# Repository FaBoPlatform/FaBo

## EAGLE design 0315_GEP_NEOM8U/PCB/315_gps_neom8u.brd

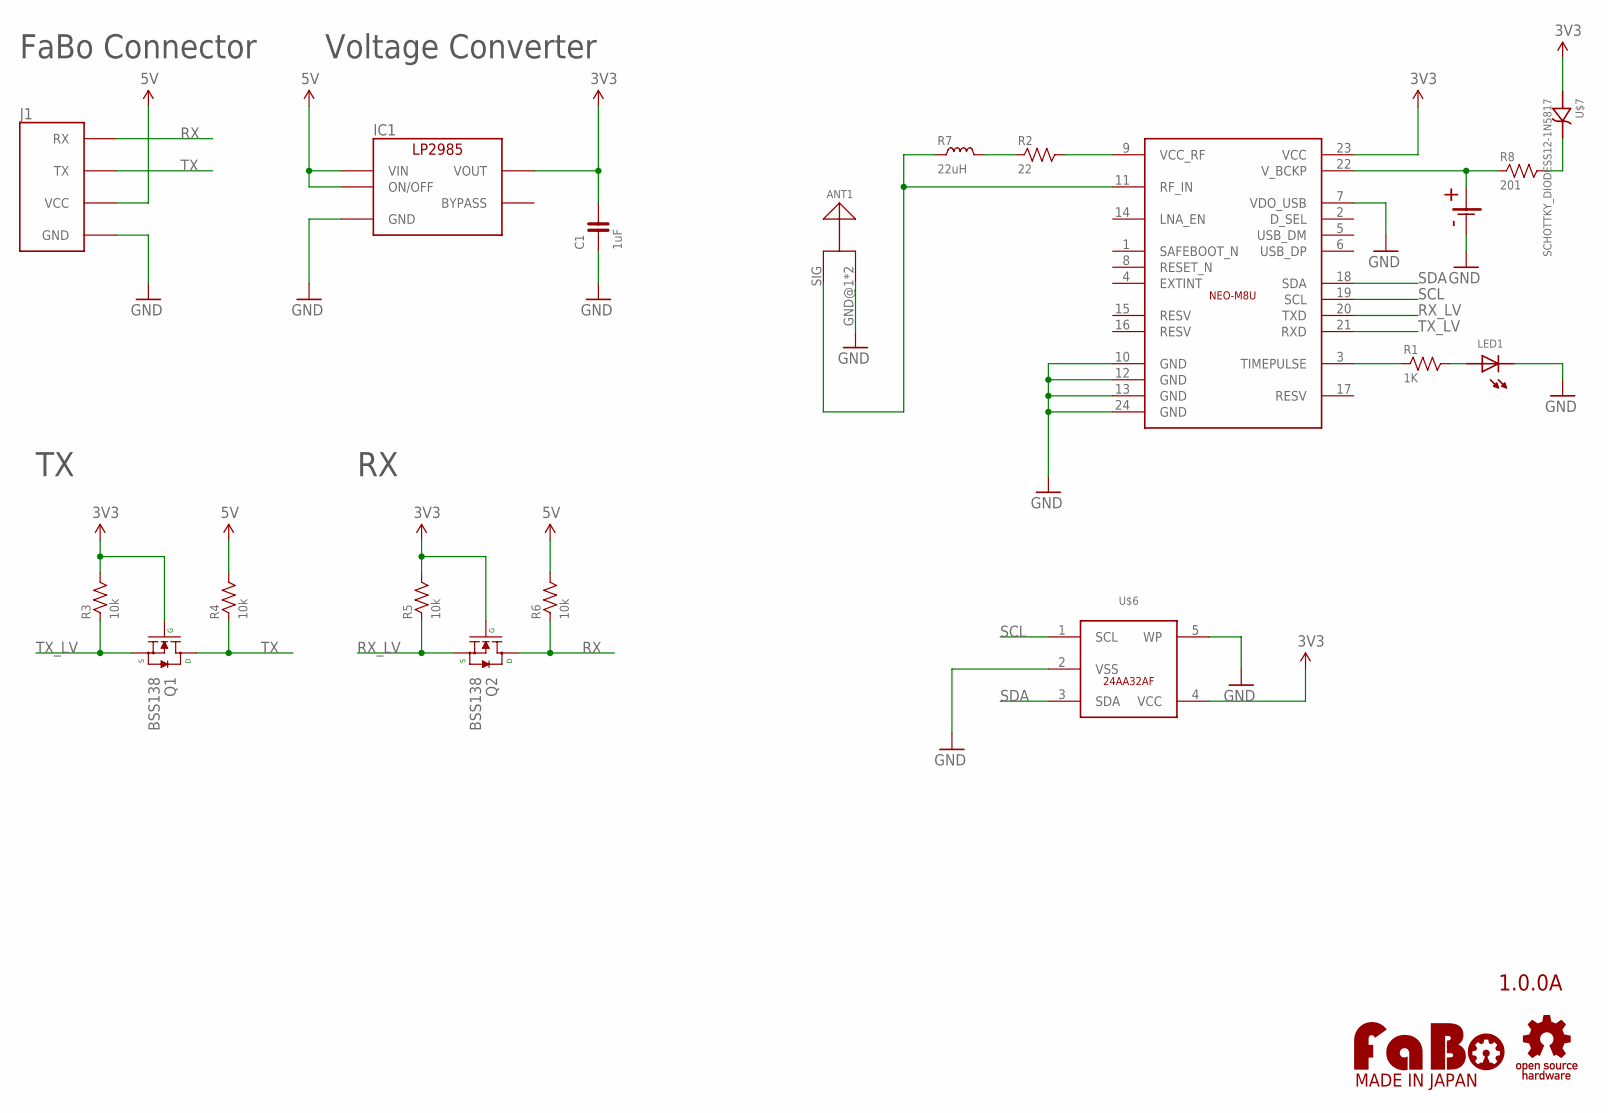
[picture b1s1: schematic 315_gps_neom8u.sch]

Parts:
ANT1: ANTENA_HIROSE-UF-L; HIROSE-UF-L
C1: 1uF; 0603-NARROW
IC1: LP2985-33DBV; SOT-23-5
J1: FABO_BRICK_SERIAL
LED1: LED-0603; 0603
Q1, Q2: BSS138; SOT23-3
R1: 1K; 0603-NARROW
R2: 22; 0603-NARROW
R3, R4, R5, R6: 10k; 0603-NARROW
R7: 22uH; 0603
R8: 201; 0603-NARROW
U$2: LOGO_OSHW-M_BOTTOM; LOGO_OSHW_M_BOTTOM
U$3: LOGO_FABO-M_BOTTOM; LOGO_FABO_MS_BOTTOM
U$4: NEO-M8U; NEO-M8M
U$6: 24AA32AF
U$7: SCHOTTKY_DIODESS12-1N5817; DO-214AC
U$10: COILCELLBK-885-BOTTOM; BK-885

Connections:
3V3: C1.2, IC1.5 (VOUT), Q1.1 (G), Q2.1 (G), R3.2, R5.2, U$4.23 (VCC), U$6.4 (VCC), U$7.CATHODE
5V: IC1.1 (VIN), IC1.3 (ON/OFF), J1.VCC, R4.2, R6.2
GND: ANT1.GND@1 (GND), ANT1.GND@2 (GND), C1.1, IC1.2 (GND), J1.GND, LED1.CATHODE, U$4.7 (VDO_USB), U$4.10 (GND), U$4.12 (GND), U$4.13 (GND), U$4.24 (GND), U$6.2 (VSS), U$6.5 (WP), U$10.GND1 (-), U$10.GND2 (-)
unnamed: R1.1, U$4.3 (TIMEPULSE)
unnamed: LED1.ANODE, R1.2
unnamed: R8.2, U$7.ANODE
unnamed: R8.1, U$4.22 (V_BCKP), U$10.VCC (+)
unnamed: R2.2, U$4.9 (VCC_RF)
unnamed: R2.1, R7.2
unnamed: ANT1.SIG, R7.1, U$4.11 (RF_IN)
RX: J1.RX, Q2.3 (D), R6.1
RX_LV: Q2.2 (S), R5.1, U$4.20 (TXD)
SCL: U$4.19 (SCL), U$6.1 (SCL)
SDA: U$4.18 (SDA), U$6.3 (SDA)
TX: J1.TX, Q1.3 (D), R4.1
TX_LV: Q1.2 (S), R3.1, U$4.21 (RXD)

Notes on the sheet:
1.0.0A
Voltage Converter
FaBo Connector

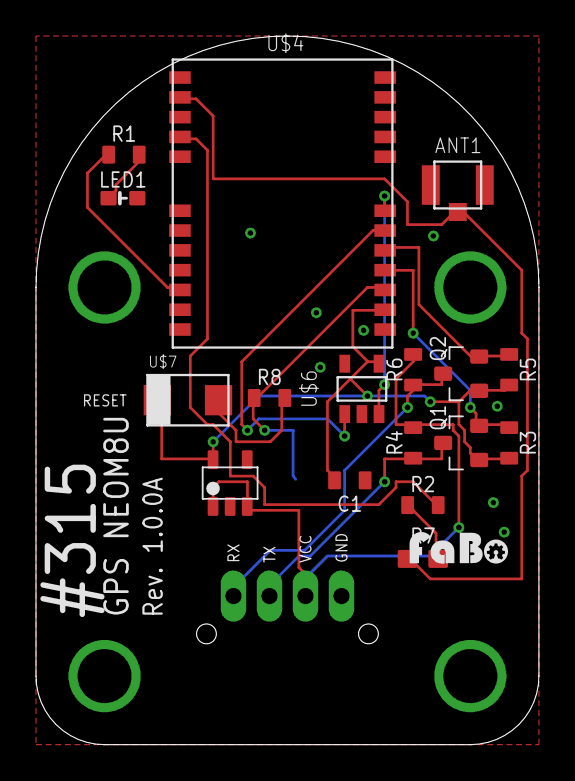
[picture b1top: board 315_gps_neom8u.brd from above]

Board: 2 copper layers, 27.9 x 39.4 mm, 22 parts (0 on the bottom side), 16 nets.

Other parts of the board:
U$5: LOGO_FABO_S

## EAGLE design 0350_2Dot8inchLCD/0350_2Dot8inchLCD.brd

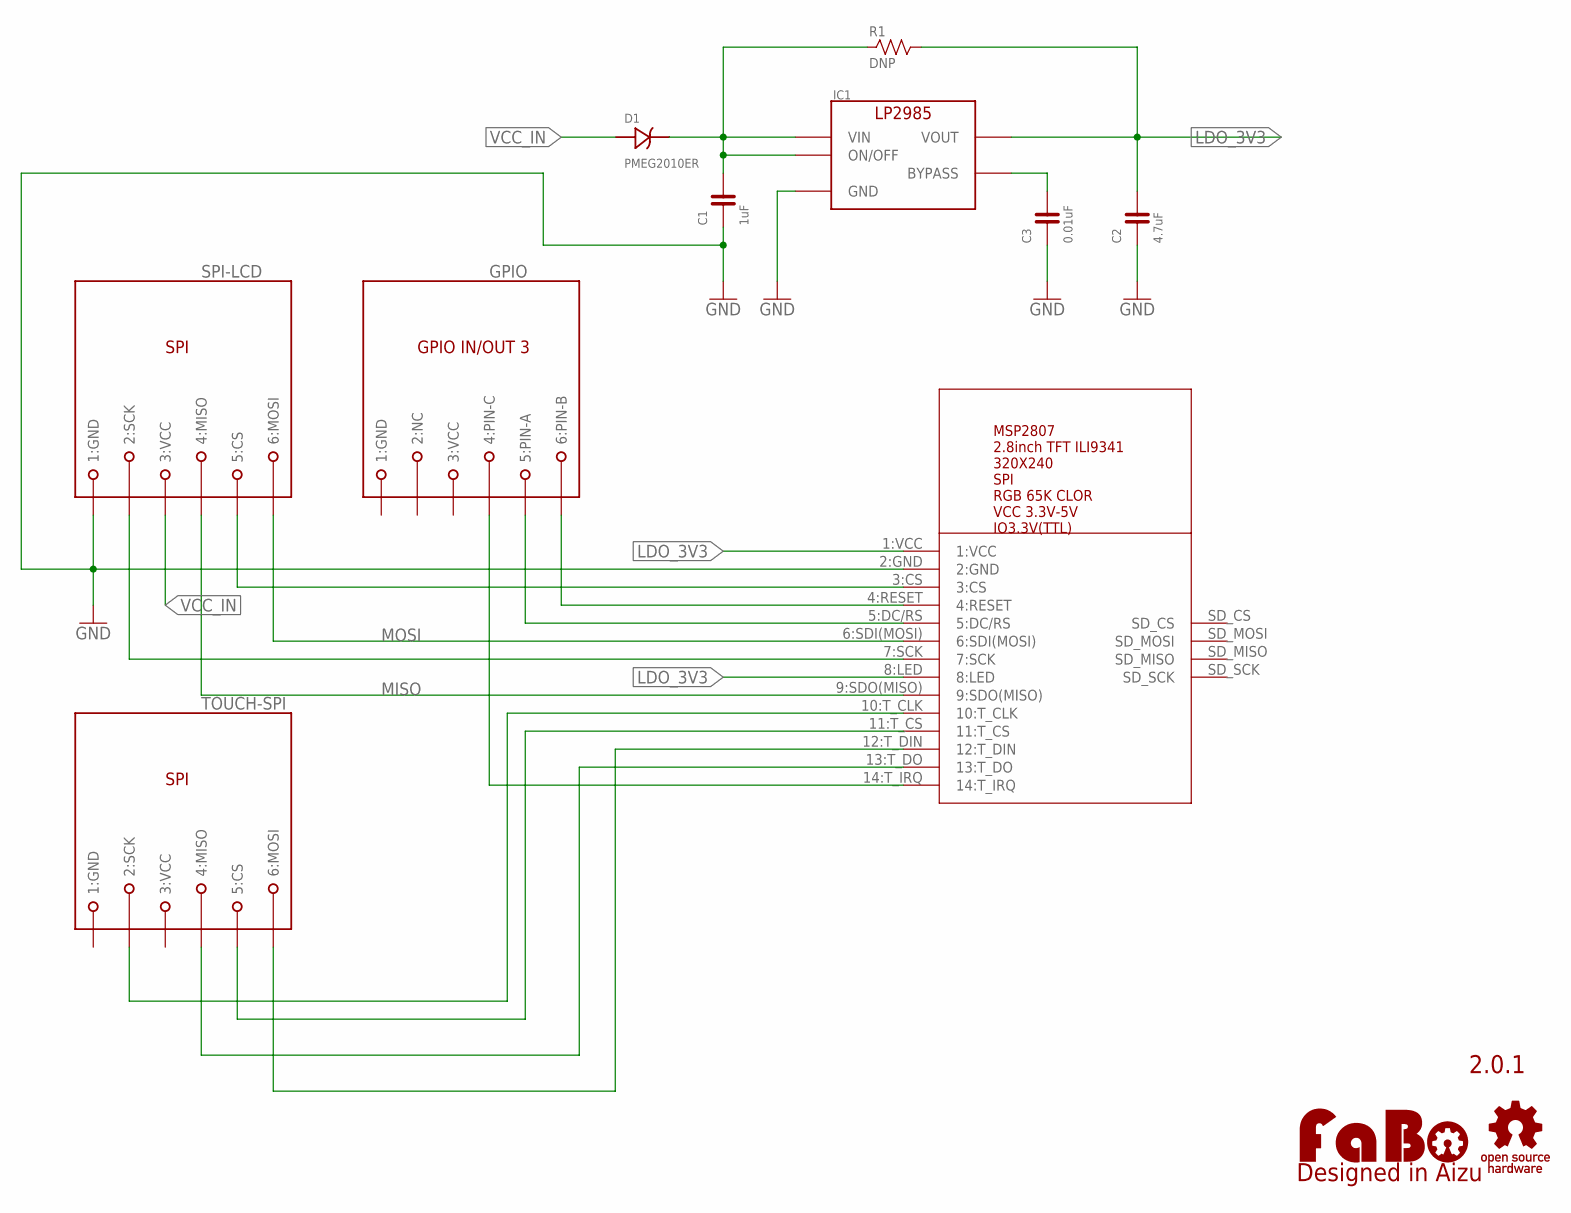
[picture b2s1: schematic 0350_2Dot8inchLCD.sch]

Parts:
C1: 1uF; 0603
C2: 4.7uF; 0603
C3: 0.01uF; 0603
D1: PMEG2010ER; SOD123W
GPIO: MODULAR-JACK-6P-RJ11_GPIO3; 7002-6PXC-X
IC1: LP2985-33DBV; SOT-23-5
LOGO1: LOGO_FABO-M_BOTTOM; LOGO_FABO_M_BOTTOM
R1: DNP; 0805
SPI-LCD: MODULAR-JACK-6P-RJ11_SPI; 7002-6PXC-X
TOUCH-SPI: MODULAR-JACK-6P-RJ11_SPI; 7002-6PXC-X
U$3: LOGO_OSHW-M_BOTTOM; LOGO_OSHW_M_BOTTOM
U$5: MSP2807(LCD_SPI); SPI_LCD_MSP2807

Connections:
1:GND: GPIO.1 (1:GND), TOUCH-SPI.1 (1:GND)
3:VCC: GPIO.3 (3:VCC), TOUCH-SPI.3 (3:VCC)
GND: C1.1, C2.1, C3.1, IC1.2 (GND), SPI-LCD.1 (1:GND), U$5.2:GND
LDO_3V3: C2.2, IC1.5 (VOUT), R1.2, U$5.1:VCC, U$5.8:LED
MISO: SPI-LCD.4 (4:MISO), U$5.9:SDO(MISO)
MOSI: SPI-LCD.6 (6:MOSI), U$5.6:SDI(MOSI)
unnamed: C1.2, D1.1 (CATHODE), IC1.1 (VIN), IC1.3 (ON/OFF), R1.1
unnamed: C3.2, IC1.4 (BYPASS)
unnamed: SPI-LCD.2 (2:SCK), U$5.7:SCK
unnamed: SPI-LCD.5 (5:CS), U$5.3:CS
unnamed: GPIO.6 (6:PIN-B), U$5.4:RESET
unnamed: GPIO.5 (5:PIN-A), U$5.5:DC/RS
unnamed: TOUCH-SPI.2 (2:SCK), U$5.10:T_CLK
unnamed: TOUCH-SPI.5 (5:CS), U$5.11:T_CS
unnamed: TOUCH-SPI.4 (4:MISO), U$5.13:T_DO
unnamed: TOUCH-SPI.6 (6:MOSI), U$5.12:T_DIN
unnamed: GPIO.4 (4:PIN-C), U$5.14:T_IRQ
VCC_IN: D1.2 (ANODE), SPI-LCD.3 (3:VCC)

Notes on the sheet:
2.0.1

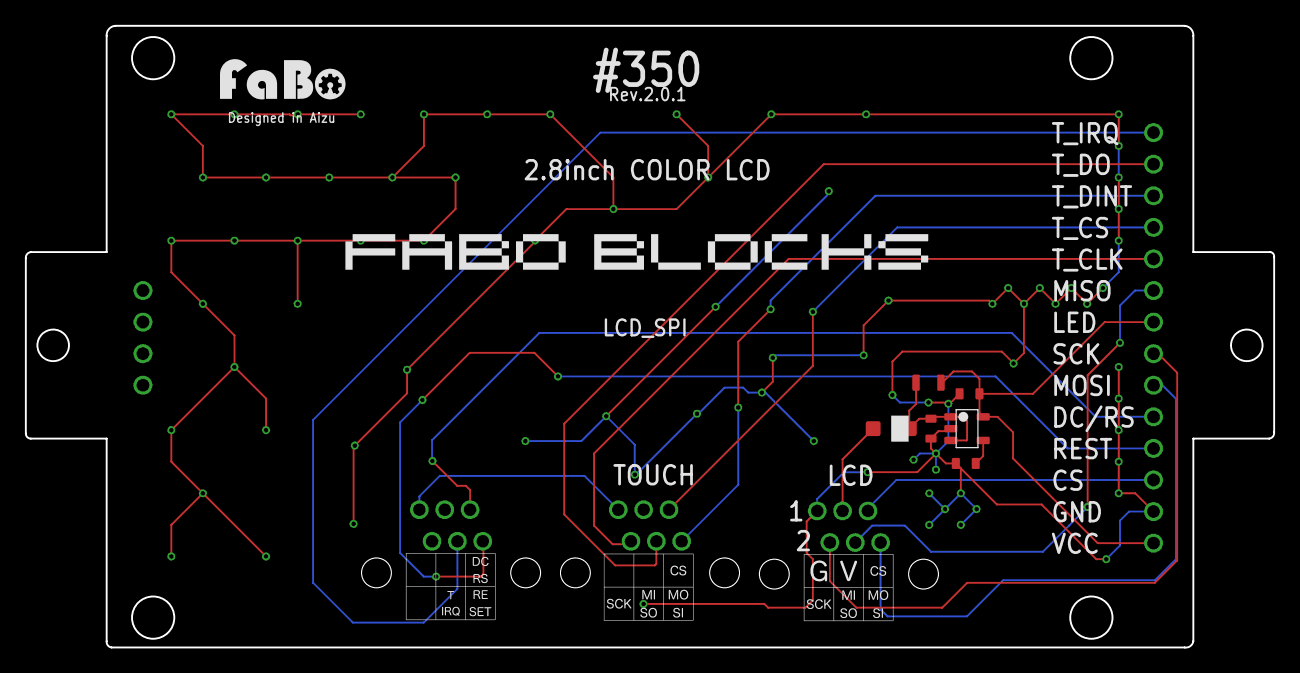
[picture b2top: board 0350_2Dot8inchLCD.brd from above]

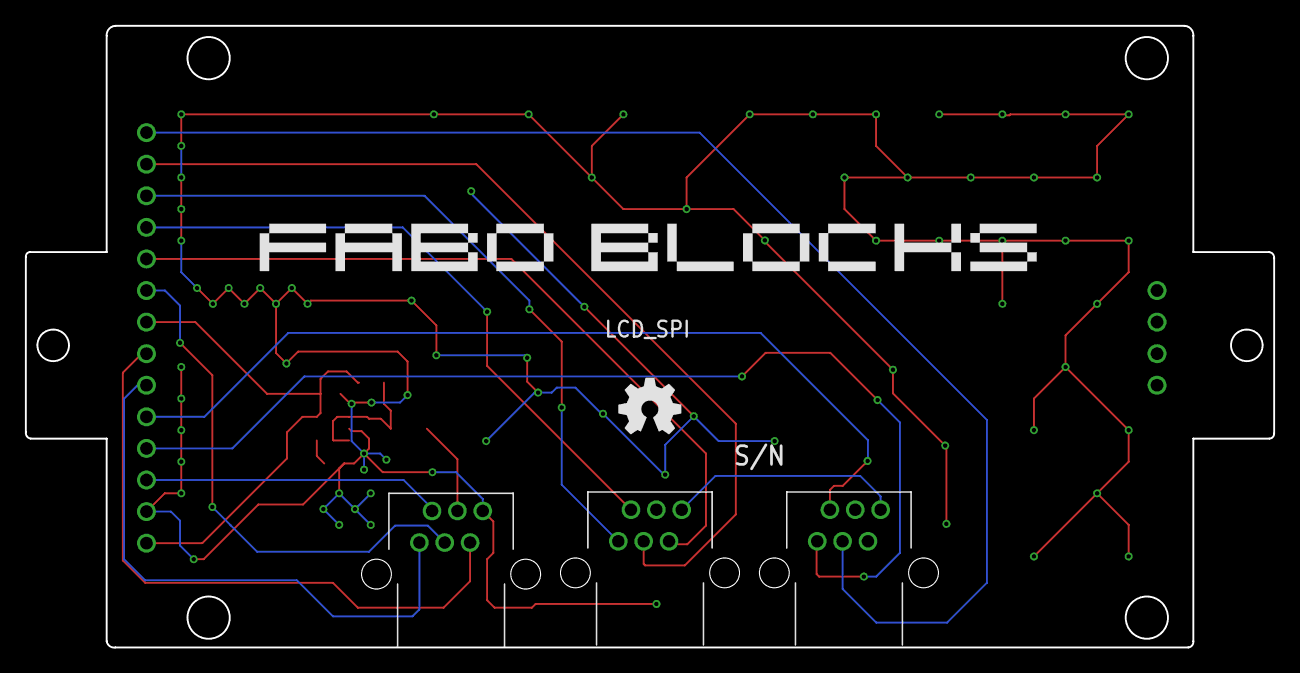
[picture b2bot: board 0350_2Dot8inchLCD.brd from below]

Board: 2 copper layers, 100.4 x 50.0 mm, 14 parts (4 on the bottom side), 18 nets.

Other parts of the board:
U$2, U$4: 4-1BLOCK

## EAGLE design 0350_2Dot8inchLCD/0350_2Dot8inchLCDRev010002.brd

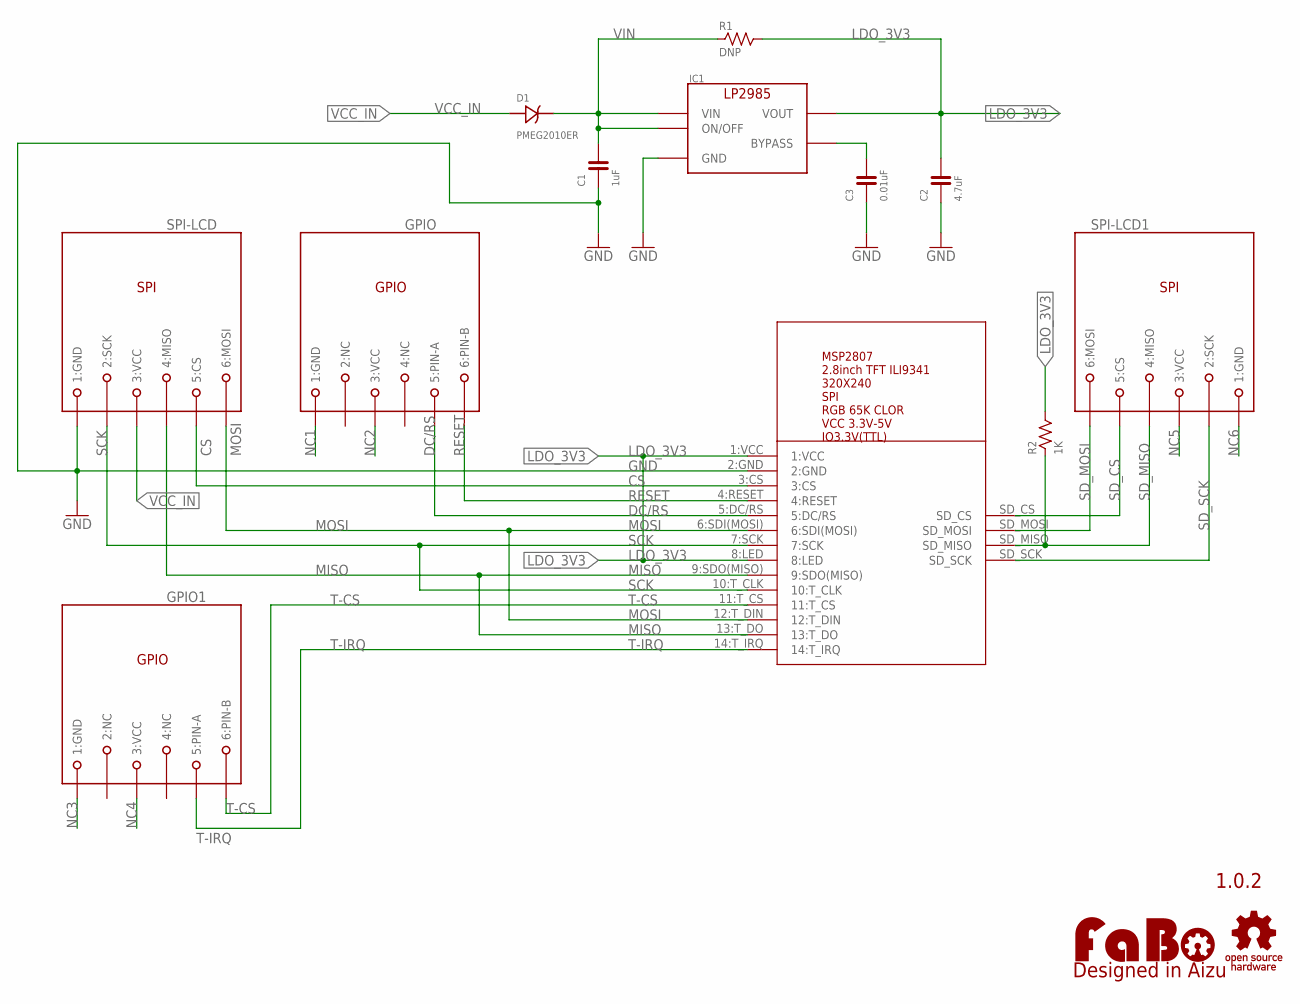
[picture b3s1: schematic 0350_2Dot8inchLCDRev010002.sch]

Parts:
C1: 1uF; 0603
C2: 4.7uF; 0603
C3: 0.01uF; 0603
D1: PMEG2010ER; SOD123W
GPIO, GPIO1: MODULAR-JACK-6P-RJ11_GPIO; 7002-6PXC-X
IC1: LP2985-33DBV; SOT-23-5
LOGO1: LOGO_FABO-M_BOTTOM; LOGO_FABO_M_BOTTOM
R1: DNP; 0805
R2: 1K; 0805
SPI-LCD, SPI-LCD1: MODULAR-JACK-6P-RJ11_SPI; 7002-6PXC-X
U$3: LOGO_OSHW-M_BOTTOM; LOGO_OSHW_M_BOTTOM
U$6: MSP2807(LCD_SPI_WITH_SDCARD; SPI_LCD_MSP2807

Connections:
CS: SPI-LCD.5 (5:CS), U$6.3:CS
DC/RS: GPIO.5 (5:PIN-A), U$6.5:DC/RS
GND: C1.1, C2.1, C3.1, IC1.2 (GND), SPI-LCD.1 (1:GND), U$6.2:GND
LDO_3V3: C2.2, IC1.5 (VOUT), R1.2, R2.2, U$6.1:VCC, U$6.8:LED
MISO: SPI-LCD.4 (4:MISO), U$6.9:SDO(MISO), U$6.13:T_DO
MOSI: SPI-LCD.6 (6:MOSI), U$6.6:SDI(MOSI), U$6.12:T_DIN
unnamed: C3.2, IC1.4 (BYPASS)
NC1: GPIO.1 (1:GND)
NC2: GPIO.3 (3:VCC)
NC3: GPIO1.1 (1:GND)
NC4: GPIO1.3 (3:VCC)
NC5: SPI-LCD1.3 (3:VCC)
NC6: SPI-LCD1.1 (1:GND)
RESET: GPIO.6 (6:PIN-B), U$6.4:RESET
SCK: SPI-LCD.2 (2:SCK), U$6.7:SCK, U$6.10:T_CLK
SD_CS: SPI-LCD1.5 (5:CS), U$6.SD_CS
SD_MISO: R2.1, SPI-LCD1.4 (4:MISO), U$6.SD_MISO
SD_MOSI: SPI-LCD1.6 (6:MOSI), U$6.SD_MOSI
SD_SCK: SPI-LCD1.2 (2:SCK), U$6.SD_SCK
T-CS: GPIO1.6 (6:PIN-B), U$6.11:T_CS
T-IRQ: GPIO1.5 (5:PIN-A), U$6.14:T_IRQ
VCC_IN: D1.2 (ANODE), SPI-LCD.3 (3:VCC)
VIN: C1.2, D1.1 (CATHODE), IC1.1 (VIN), IC1.3 (ON/OFF), R1.1

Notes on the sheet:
1.0.2

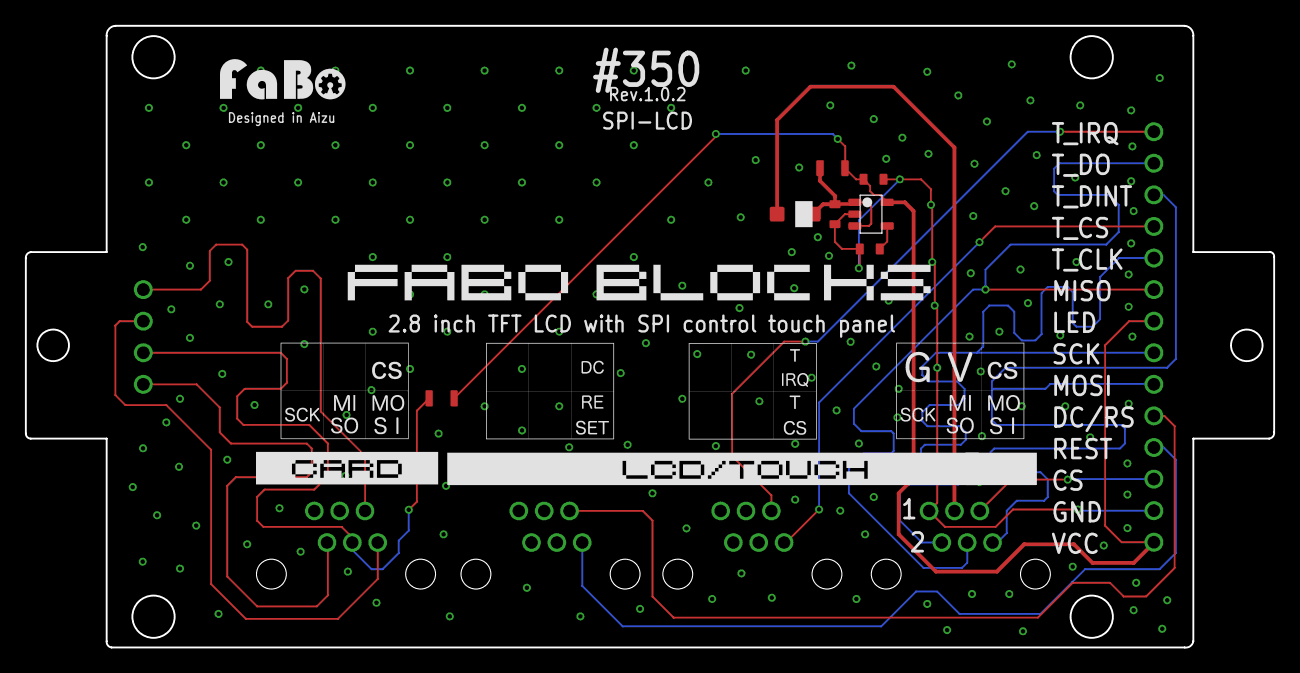
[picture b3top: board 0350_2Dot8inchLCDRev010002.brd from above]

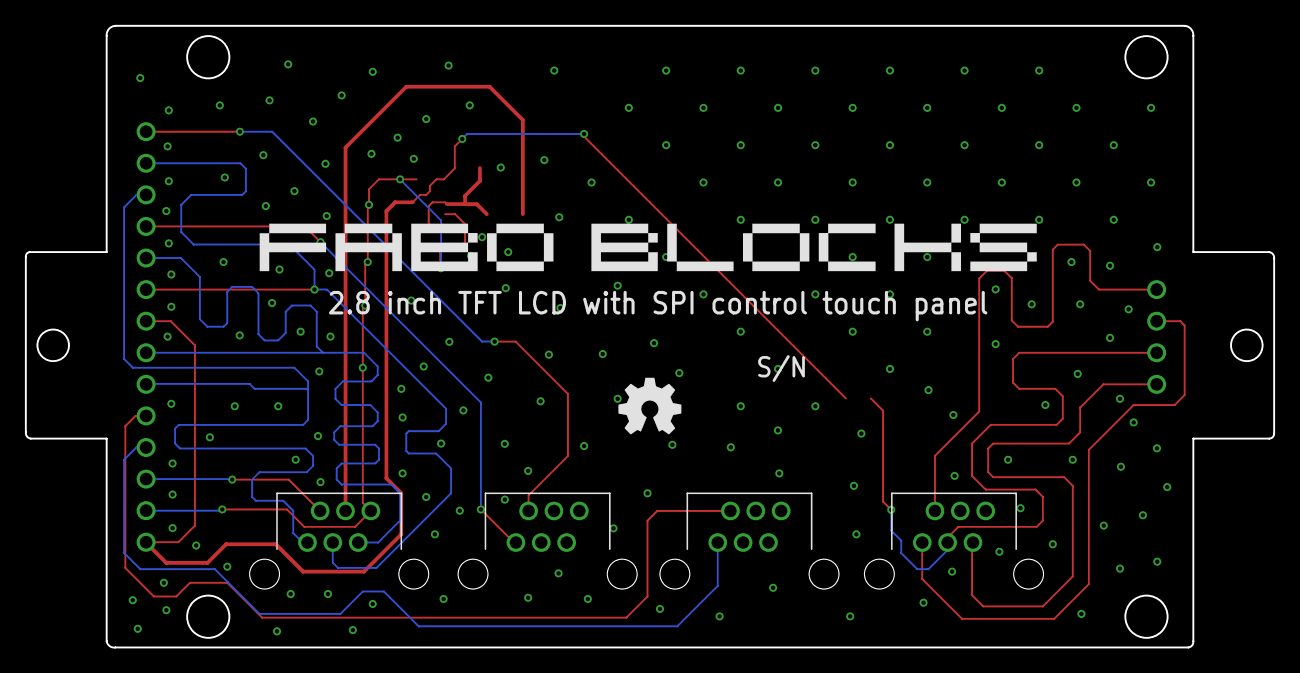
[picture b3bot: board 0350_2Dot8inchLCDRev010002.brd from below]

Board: 2 copper layers, 100.4 x 50.0 mm, 16 parts (5 on the bottom side), 17 nets.

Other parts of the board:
U$2, U$4: 4-1BLOCK

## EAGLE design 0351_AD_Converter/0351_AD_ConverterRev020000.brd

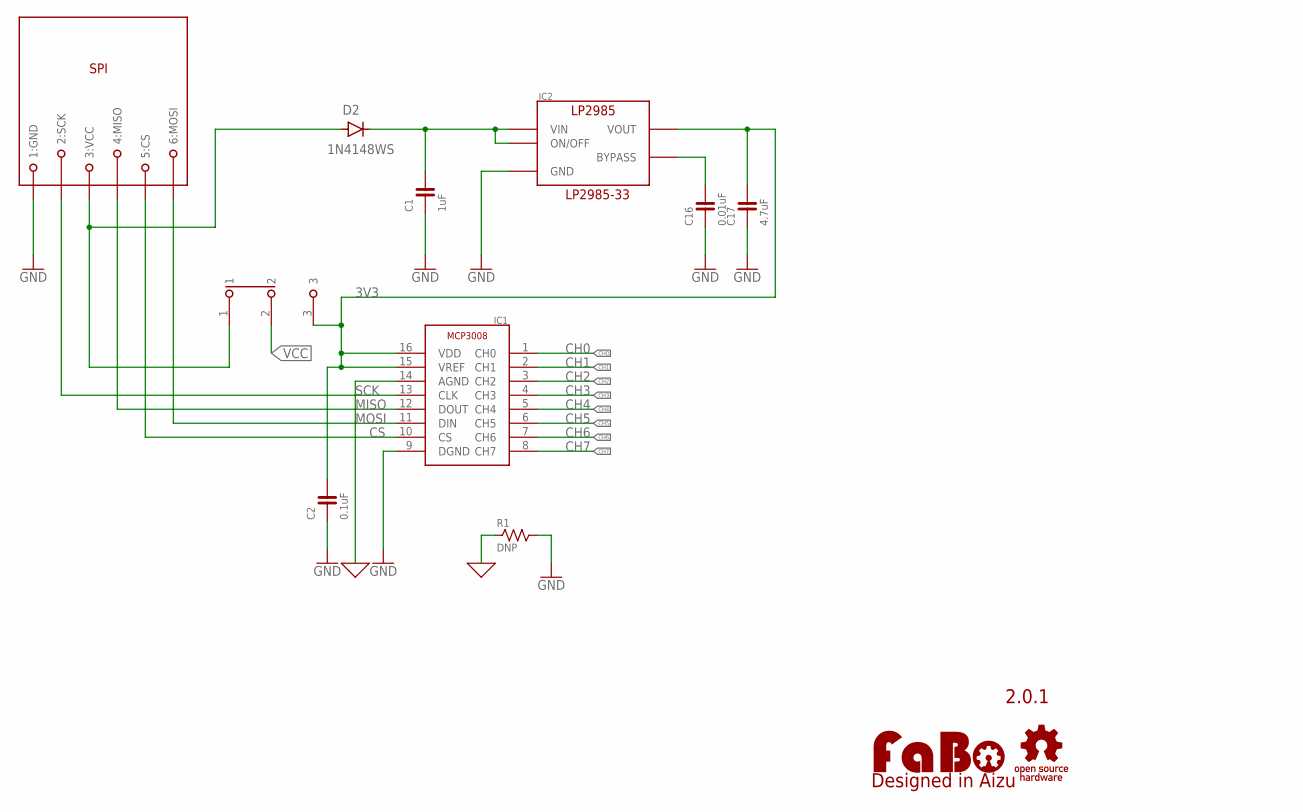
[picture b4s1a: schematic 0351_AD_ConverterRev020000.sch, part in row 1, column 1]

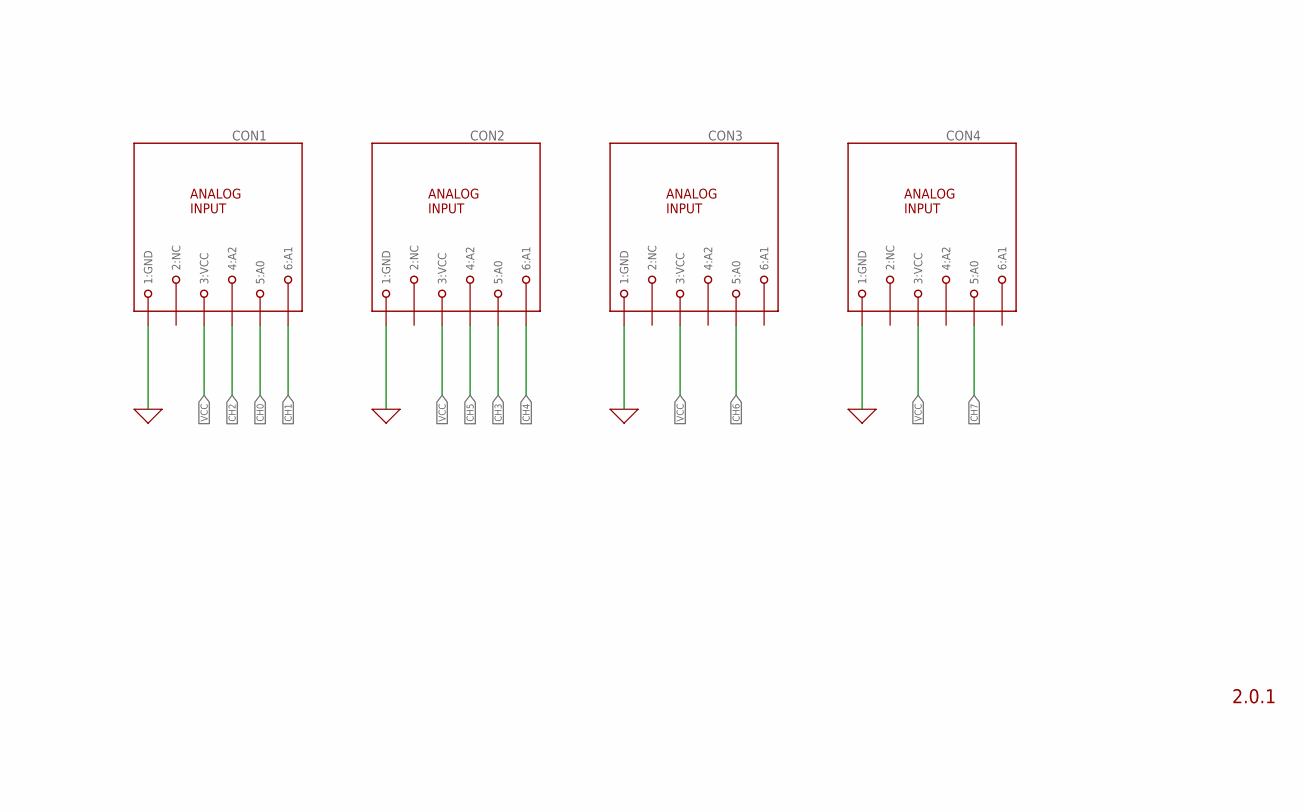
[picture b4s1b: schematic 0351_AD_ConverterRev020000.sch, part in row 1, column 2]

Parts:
C1: 1uF; 0603
C2: 0.1uF; 0603
C16: 0.01uF; 0603
C17: 4.7uF; 0603
CON1, CON2, CON3, CON4: MODULAR-JACK-6P-RJ11_ANALOG3; 7002-6PXC-X
D2: 1N4148WS; SOD-323
IC1: MICROCHIP-MCP3008
IC2: LP2985-33DBV; SOT-23-5
LCD-SPI_RJ11: MODULAR-JACK-6P-RJ11_SPI; 7002-6PXC-X
LOGO1: LOGO_FABO-M_BOTTOM; LOGO_FABO_M_BOTTOM
R1: DNP; 0805
U$3: LOGO_OSHW-M_BOTTOM; LOGO_OSHW_M_BOTTOM
U$5: SSSS213202

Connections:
3V3: C2.2, C17.2, IC1.15 (VREF), IC1.16 (VDD), IC2.5 (VOUT), U$5.3
AGND: CON1.1 (1:GND), CON2.1 (1:GND), CON3.1 (1:GND), CON4.1 (1:GND), IC1.14 (AGND), R1.1
CH0: CON1.5 (5:A0), IC1.1 (CH0)
CH1: CON1.6 (6:A1), IC1.2 (CH1)
CH2: CON1.4 (4:A2), IC1.3 (CH2)
CH3: CON2.5 (5:A0), IC1.4 (CH3)
CH4: CON2.6 (6:A1), IC1.5 (CH4)
CH5: CON2.4 (4:A2), IC1.6 (CH5)
CH6: CON3.5 (5:A0), IC1.7 (CH6)
CH7: CON4.5 (5:A0), IC1.8 (CH7)
CS: IC1.10 (CS), LCD-SPI_RJ11.5 (5:CS)
GND: C1.1, C2.1, C16.1, C17.1, IC1.9 (DGND), IC2.2 (GND), LCD-SPI_RJ11.1 (1:GND), R1.2
MISO: IC1.12 (DOUT), LCD-SPI_RJ11.4 (4:MISO)
MOSI: IC1.11 (DIN), LCD-SPI_RJ11.6 (6:MOSI)
unnamed: C16.2, IC2.4 (BYPASS)
unnamed: C1.2, D2.C, IC2.1 (VIN), IC2.3 (ON/OFF)
SCK: IC1.13 (CLK), LCD-SPI_RJ11.2 (2:SCK)
VCC: CON1.3 (3:VCC), CON2.3 (3:VCC), CON3.3 (3:VCC), CON4.3 (3:VCC), U$5.2
VCC_IN: D2.A, LCD-SPI_RJ11.3 (3:VCC), U$5.1

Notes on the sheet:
2.0.1
LP2985-33

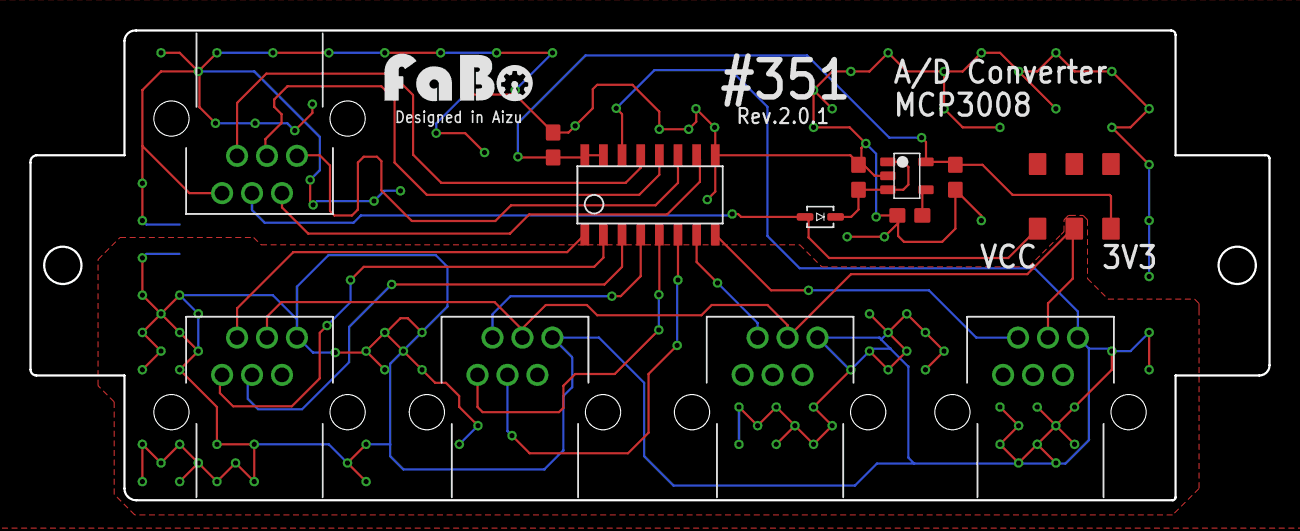
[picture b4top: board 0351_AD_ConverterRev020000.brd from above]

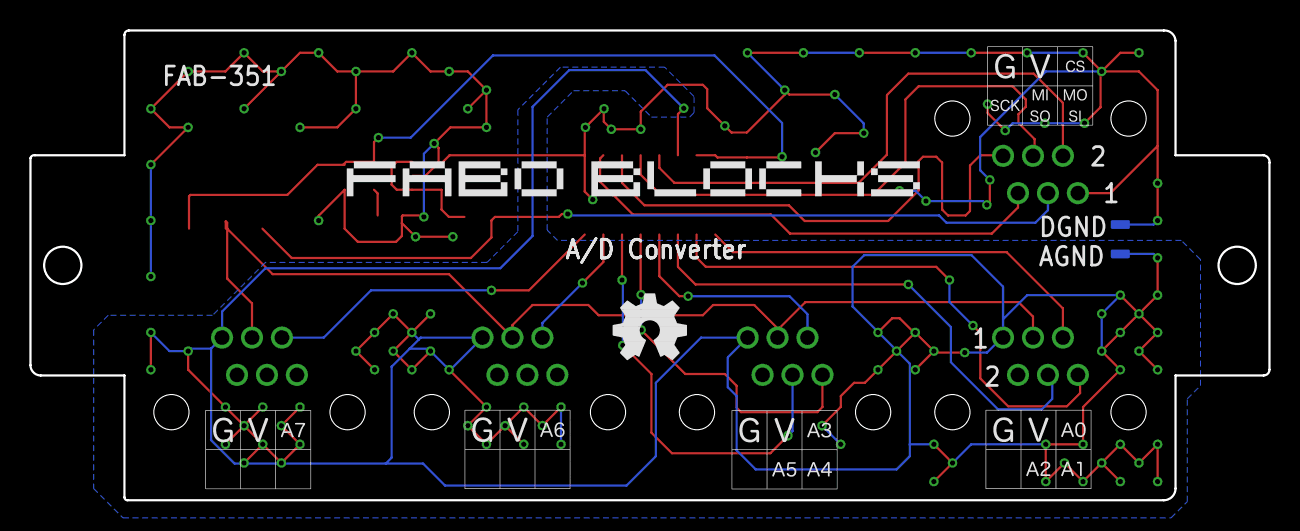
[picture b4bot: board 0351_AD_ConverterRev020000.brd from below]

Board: 2 copper layers, 84.4 x 32.0 mm, 18 parts (2 on the bottom side), 19 nets.

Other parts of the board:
U$2, U$4: 4-1BLOCK

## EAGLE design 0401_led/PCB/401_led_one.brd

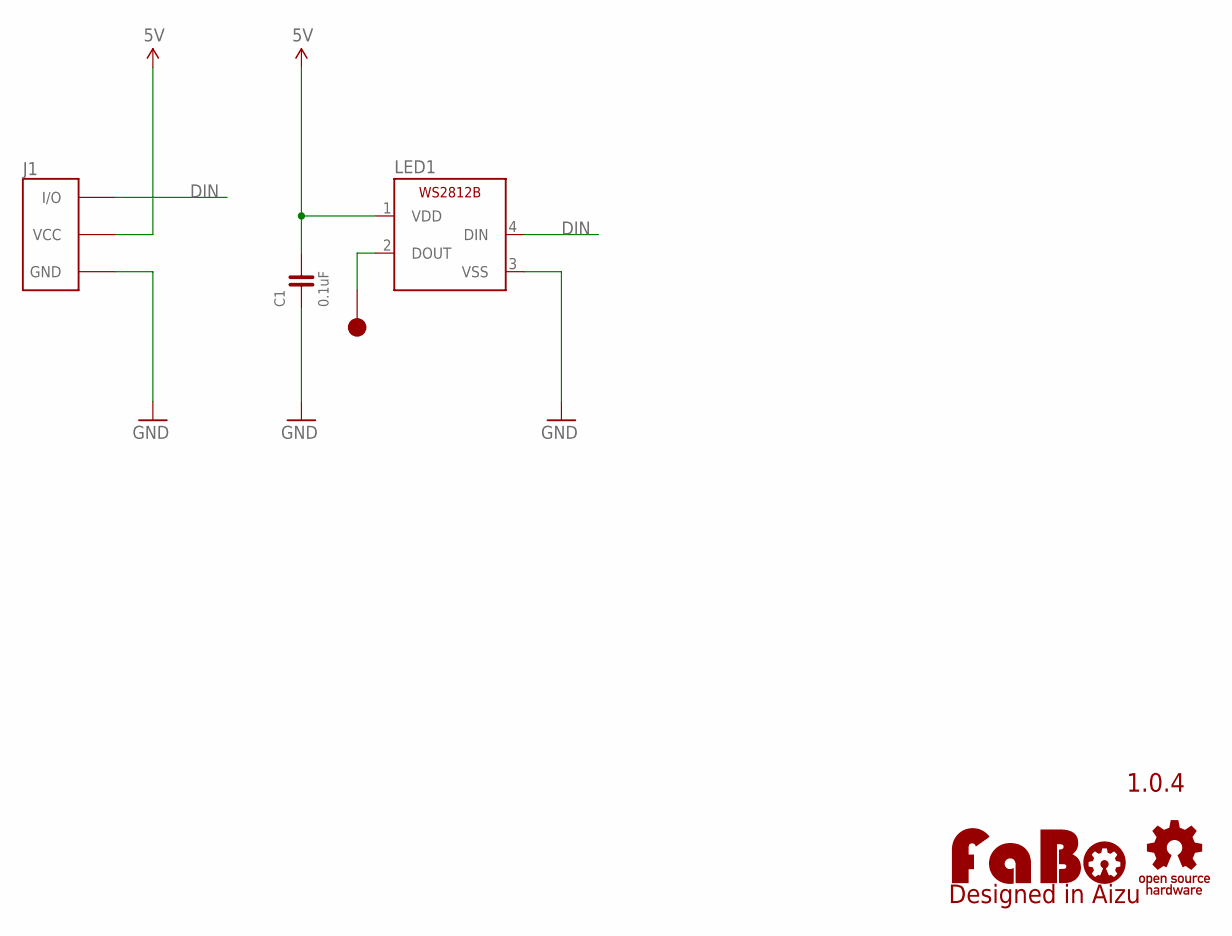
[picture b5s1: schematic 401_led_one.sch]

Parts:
C1: 0.1uF; 0603
J1: FABO_BRICK_3PIN
LED1: WS2812B
LOGO1: LOGO_FABO-M; LOGO_FABO_M
TP1: TP-15
U$2: LOGO_OSHW-M_BOTTOM; LOGO_OSHW_M_BOTTOM

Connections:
5V: C1.2, J1.VCC, LED1.1 (VDD)
DIN: J1.I/O, LED1.4 (DIN)
GND: C1.1, J1.GND, LED1.3 (VSS)
unnamed: LED1.2 (DOUT), TP1.1

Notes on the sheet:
1.0.4

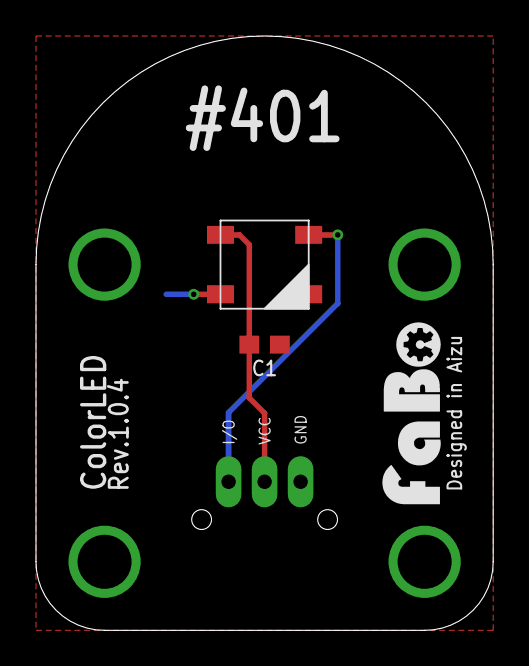
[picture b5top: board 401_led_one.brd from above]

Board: 2 copper layers, 25.4 x 33.0 mm, 6 parts (1 on the bottom side), 4 nets.

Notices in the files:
parts and their libraries:
FaBo-Template: Released under the Creative Commons Attribution-ShareAlike 4.0 License
https://creativecommons.org/licenses/by-sa/4.0
FaBo-etc: Released under the Creative Commons
